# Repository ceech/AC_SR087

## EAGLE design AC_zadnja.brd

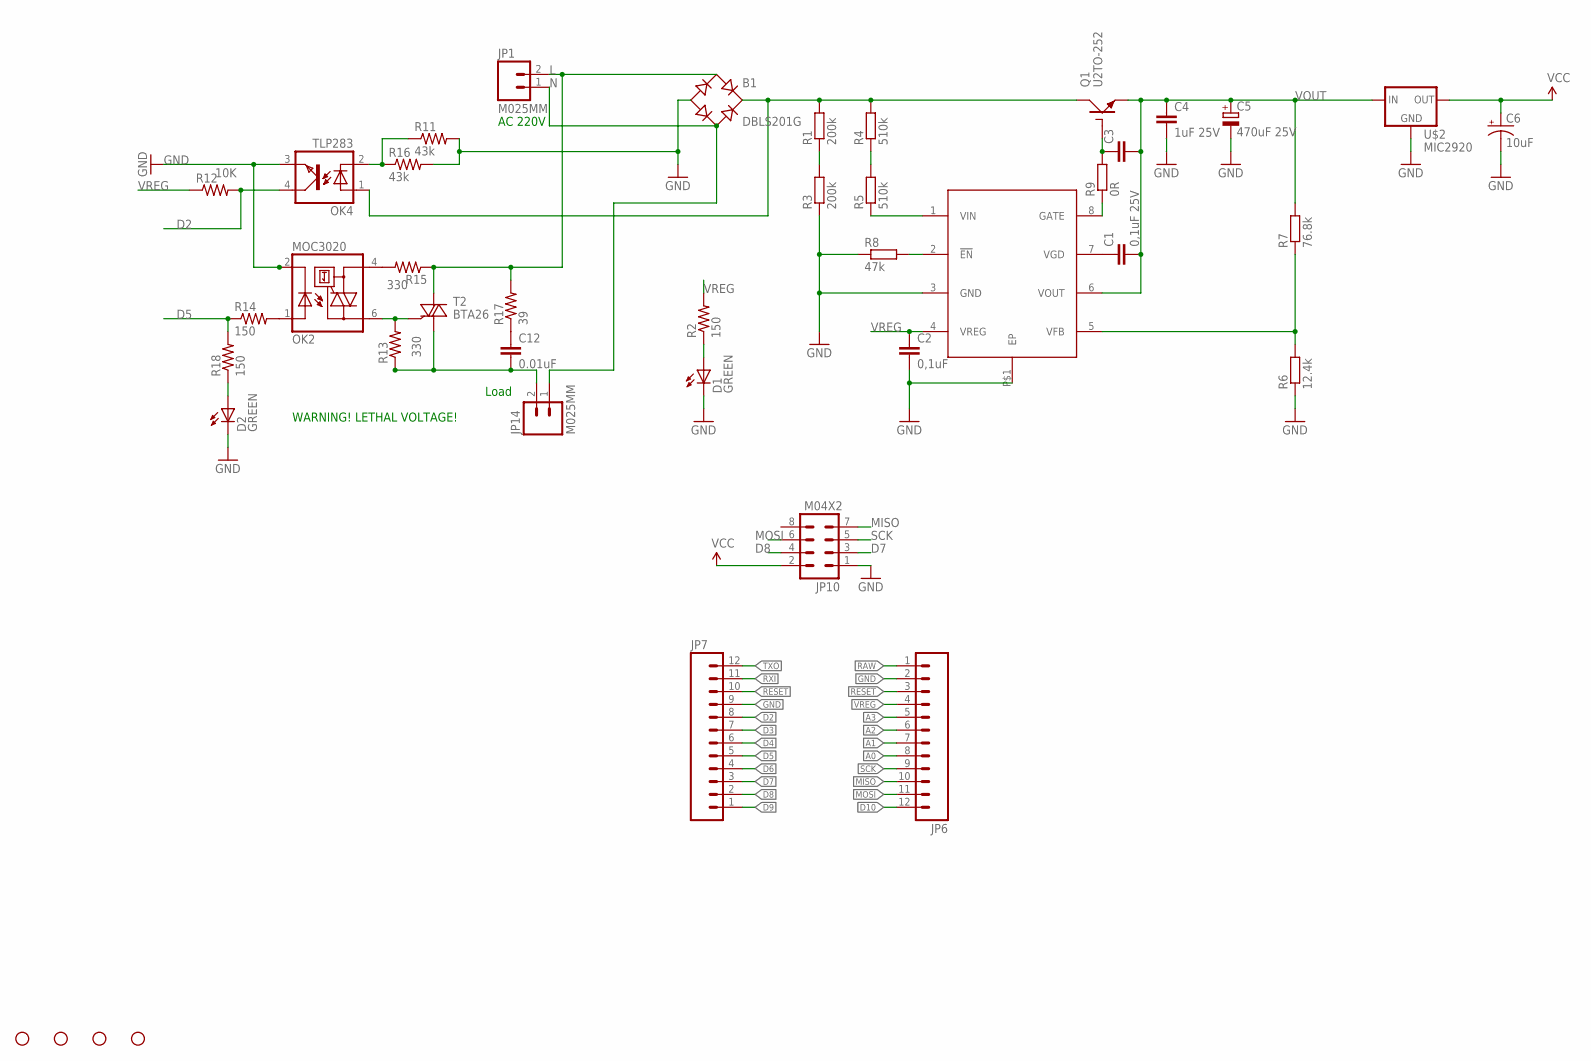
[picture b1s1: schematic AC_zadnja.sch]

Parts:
B1: DBLS201G; DBS
C1: 0,1uF 25V; C0805
C2: 0,1uF; C0805
C3: C-EUC0805; C0805
C4: 1uF 25V; C1206
C5: 470uF 25V; 153CLV-1010
C6: 10uF; EIA3216
C12: 0.01uF; C1206
D1, D2: GREEN; PLCC2
JP1, JP14: M025MM; SCREWTERMINAL-5MM-2
JP6, JP7: M12PTH; 1X12
JP10: M04X2; 2X4
OK2: MOC3020; DIL6-SMD
OK4: TLP283; MINI-FLAT-4
Q1: U2TO-252; D-PAK_TO252AA
R1, R3: 200k; M1206
R2, R14, R18: 150; 0805
R4, R5: 510k; M1206
R6: 12.4k; M0805
R7: 76.8k; M0805
R8: 47k; M0805
R9: 0R; M0805
R11, R16: 43k; 1206
R12: RESISTOR0805-RES; 0805
R13, R15: RESISTOR1206; 1206
R17: 39; 1206
STANDOFF1, STANDOFF2, STANDOFF3, STANDOFF4: STAND-OFFTIGHT; STAND-OFF-TIGHT
T2: BTA26; DPACK_2
U$1: U1; SOIC08
U$2: MIC2920; SOT223

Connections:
A0: JP6.8
A1: JP6.7
A2: JP6.6
A3: JP6.5
D2: JP7.8, OK4.4 (COL), R12.2
D3: JP7.7
D4: JP7.6
D5: JP7.5, R14.1, R18.2
D6: JP7.4
D7: JP7.3, JP10.3
D8: JP7.2, JP10.4
D9: JP7.1
D10: JP6.12
GND: B1.-, C2.2, C4.2, C5.-, C6.C (-), D1.C, D2.C, JP6.2, JP7.9, JP10.1, OK2.2 (C), OK4.3 (EMIT), R3.1, R6.1, R8.1, R11.2, R16.2, U$1.3 (GND), U$1.P$1 (EP), U$2.2 (GND)
L: B1.AC1, JP1.2, R15.1, R17.2, T2.D (A2)
MISO: JP6.10, JP10.7
MOSI: JP6.11, JP10.6
N: B1.AC2, JP1.1, JP14.1
unnamed: D1.A, R2.1
unnamed: R1.1, R3.2
unnamed: R4.1, R5.2
unnamed: R5.1, U$1.1 (VIN)
unnamed: C3.1, Q1.1 (G), R9.2
unnamed: R9.1, U$1.8 (GATE)
unnamed: R8.2, U$1.2 (!EN)
unnamed: C1.1, U$1.7 (VGD)
unnamed: R6.2, R7.1, U$1.5 (VFB)
unnamed: B1.+, OK4.1 (A), Q1.4 (C), R1.2, R4.2
unnamed: OK4.2 (C), R11.1, R16.1
unnamed: C12.2, JP14.2, R13.1, T2.G (A1)
unnamed: OK2.6 (A2), R13.2, T2.S (G)
unnamed: OK2.4 (A1), R15.2
unnamed: OK2.1 (A), R14.2
unnamed: C12.1, R17.1
unnamed: D2.A, R18.1
RAW: JP6.1
RESET: JP6.3, JP7.10
RXI: JP7.11
SCK: JP6.9, JP10.5
TXO: JP7.12
VCC: C6.A (+), JP10.2, U$2.3 (OUT)
VOUT: C1.2, C3.2, C4.1, C5.+, Q1.3 (E), R7.2, U$1.6 (VOUT), U$2.1 (IN)
VREG: C2.1, JP6.4, R2.2, R12.1, U$1.4 (VREG)

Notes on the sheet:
Load
AC 220V
WARNING! LETHAL VOLTAGE!

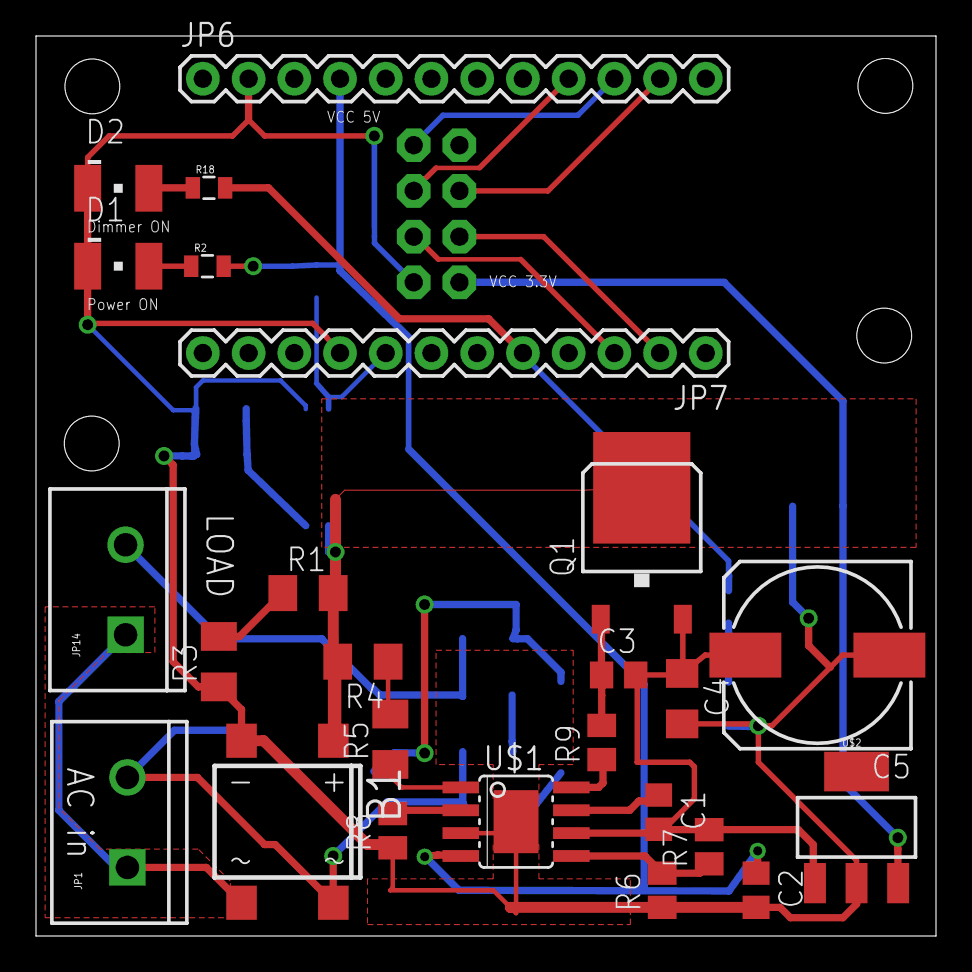
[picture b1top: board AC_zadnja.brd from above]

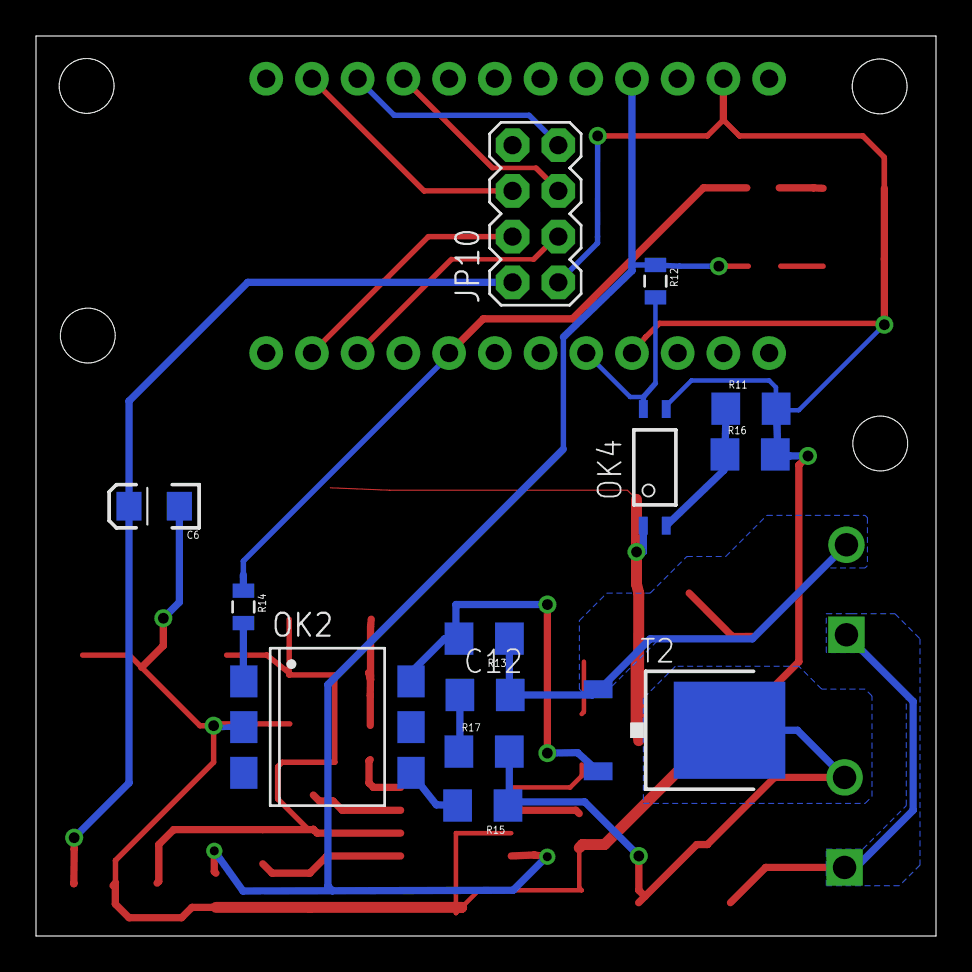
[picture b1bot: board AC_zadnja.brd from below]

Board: 2 copper layers, 50.0 x 50.0 mm, 42 parts (13 on the bottom side), 31 nets.

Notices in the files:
parts and their libraries:
SparkFun-Connectors: Licensing: Creative Commons ShareAlike 4.0 International - https://creativecommons.org/licenses/by-sa/4.0
